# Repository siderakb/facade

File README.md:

# Facade60 Keyboard

- 60% mechanical keyboard kit, 2U LShift layout
- 65 keys, Cherry MX style hot-swappable
- Gasket mount
- CNC Aluminum top case
- MJF Nylon bottom case
- USB & RP2040 MCU daughterboard
- [QMK](https://qmk.fm/) and [Vial](https://get.vial.today/) support

[Demo video](https://youtu.be/Ful9dqWGcHk)

## Structure

- Top case
- Gaskets
- Plate
- Gaskets
- Optional sound absorbing foam
- PCB
- Optional case foam
- Bottom case
- Weight

## PCB

Daughterboard PCBA available.

### Board Characteristics

- Copper layer count: 2
- Board thickness: 1.6 mm
- Board overall dimensions
    - Main board: 285 mm x 99.1 mm
    - Daughterboard: 29.25 mm x 43.75 mm
- Min track/spacing: 0.15 mm / 0.15 mm
- Min hole diameter: 0.3 mm
- Castellated pads: No
- Edge card connectors: No
- Plated board edge: No

## Case

CAD files: [onshape](https://cad.onshape.com/documents/bbbe7399d3367f05c1e650e9/w/14fd774c6821c6187949e29b/e/877617ade201dbca93eed7b8)

### Screw

- 6* M2.5x10~12, OD < 5mm, for case
- 4* M2x2, 90° flat head, for weight
- 4* M2.5x3~5, OD <3.5mm, for PCB

## Firmware

[Vial-QMK](https://github.com/siderakb/vial-qmk/tree/siderakb/main/keyboards/siderakb/facade) (*siderakb/main* branch)

## License

Hardware available under the [CERN-OHL-P v2](/LICENSE) permissive license.

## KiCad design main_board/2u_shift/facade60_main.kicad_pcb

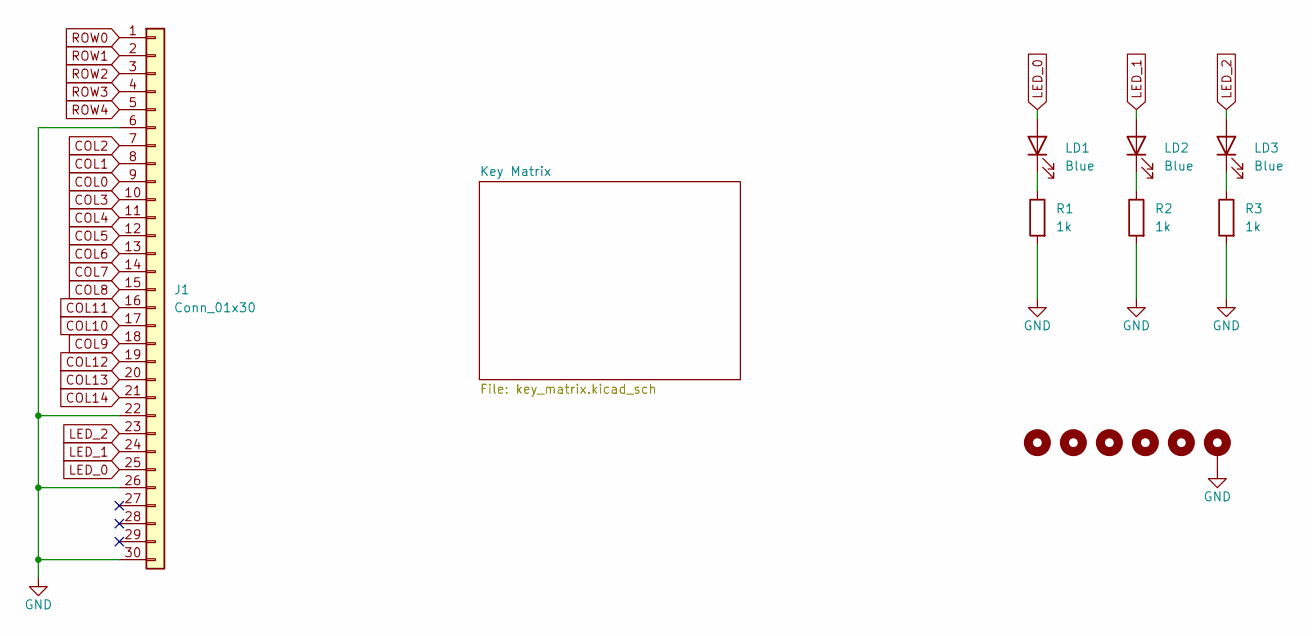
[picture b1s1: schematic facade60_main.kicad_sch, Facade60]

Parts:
H5, H6: MountingHole; MountingHole-C
H8, H9, H10: MountingHole_Pad; MountingHole-D
H11: MountingHole_Pad; MountingHole-B
J1: Conn_01x30; TE_3-1734839-0_1x30-1MP_P0.5mm_Horizontal
LD1, LD2, LD3: Blue; LED_0603_1608Metric; MFR. Part # 19-217/GHC-YR1S2/3T; LCSC C72043
R1, R2, R3: 1k; R_0603_1608Metric; MFR. Part # 0402WGF1001TCE; LCSC C11702

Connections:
COL0: J1.9; also elsewhere on the board
COL1: J1.8; also elsewhere on the board
COL2: J1.7; also elsewhere on the board
COL3: J1.10; also elsewhere on the board
COL4: J1.11; also elsewhere on the board
COL5: J1.12; also elsewhere on the board
COL6: J1.13; also elsewhere on the board
COL7: J1.14; also elsewhere on the board
COL8: J1.15; also elsewhere on the board
COL9: J1.18; also elsewhere on the board
COL10: J1.17; also elsewhere on the board
COL11: J1.16; also elsewhere on the board
COL12: J1.19; also elsewhere on the board
COL13: J1.20; also elsewhere on the board
COL14: J1.21; also elsewhere on the board
GND: H11.1, J1.6, J1.22, J1.26, J1.30, R1.2, R2.2, R3.2
LED_0: J1.25, LD1.2 (A)
LED_1: J1.24, LD2.2 (A)
LED_2: J1.23, LD3.2 (A)
unnamed: LD1.1 (K), R1.1
unnamed: LD2.1 (K), R2.1
unnamed: LD3.1 (K), R3.1
ROW0: J1.1; also elsewhere on the board
ROW1: J1.2; also elsewhere on the board
ROW2: J1.3; also elsewhere on the board
ROW3: J1.4; also elsewhere on the board
ROW4: J1.5; also elsewhere on the board

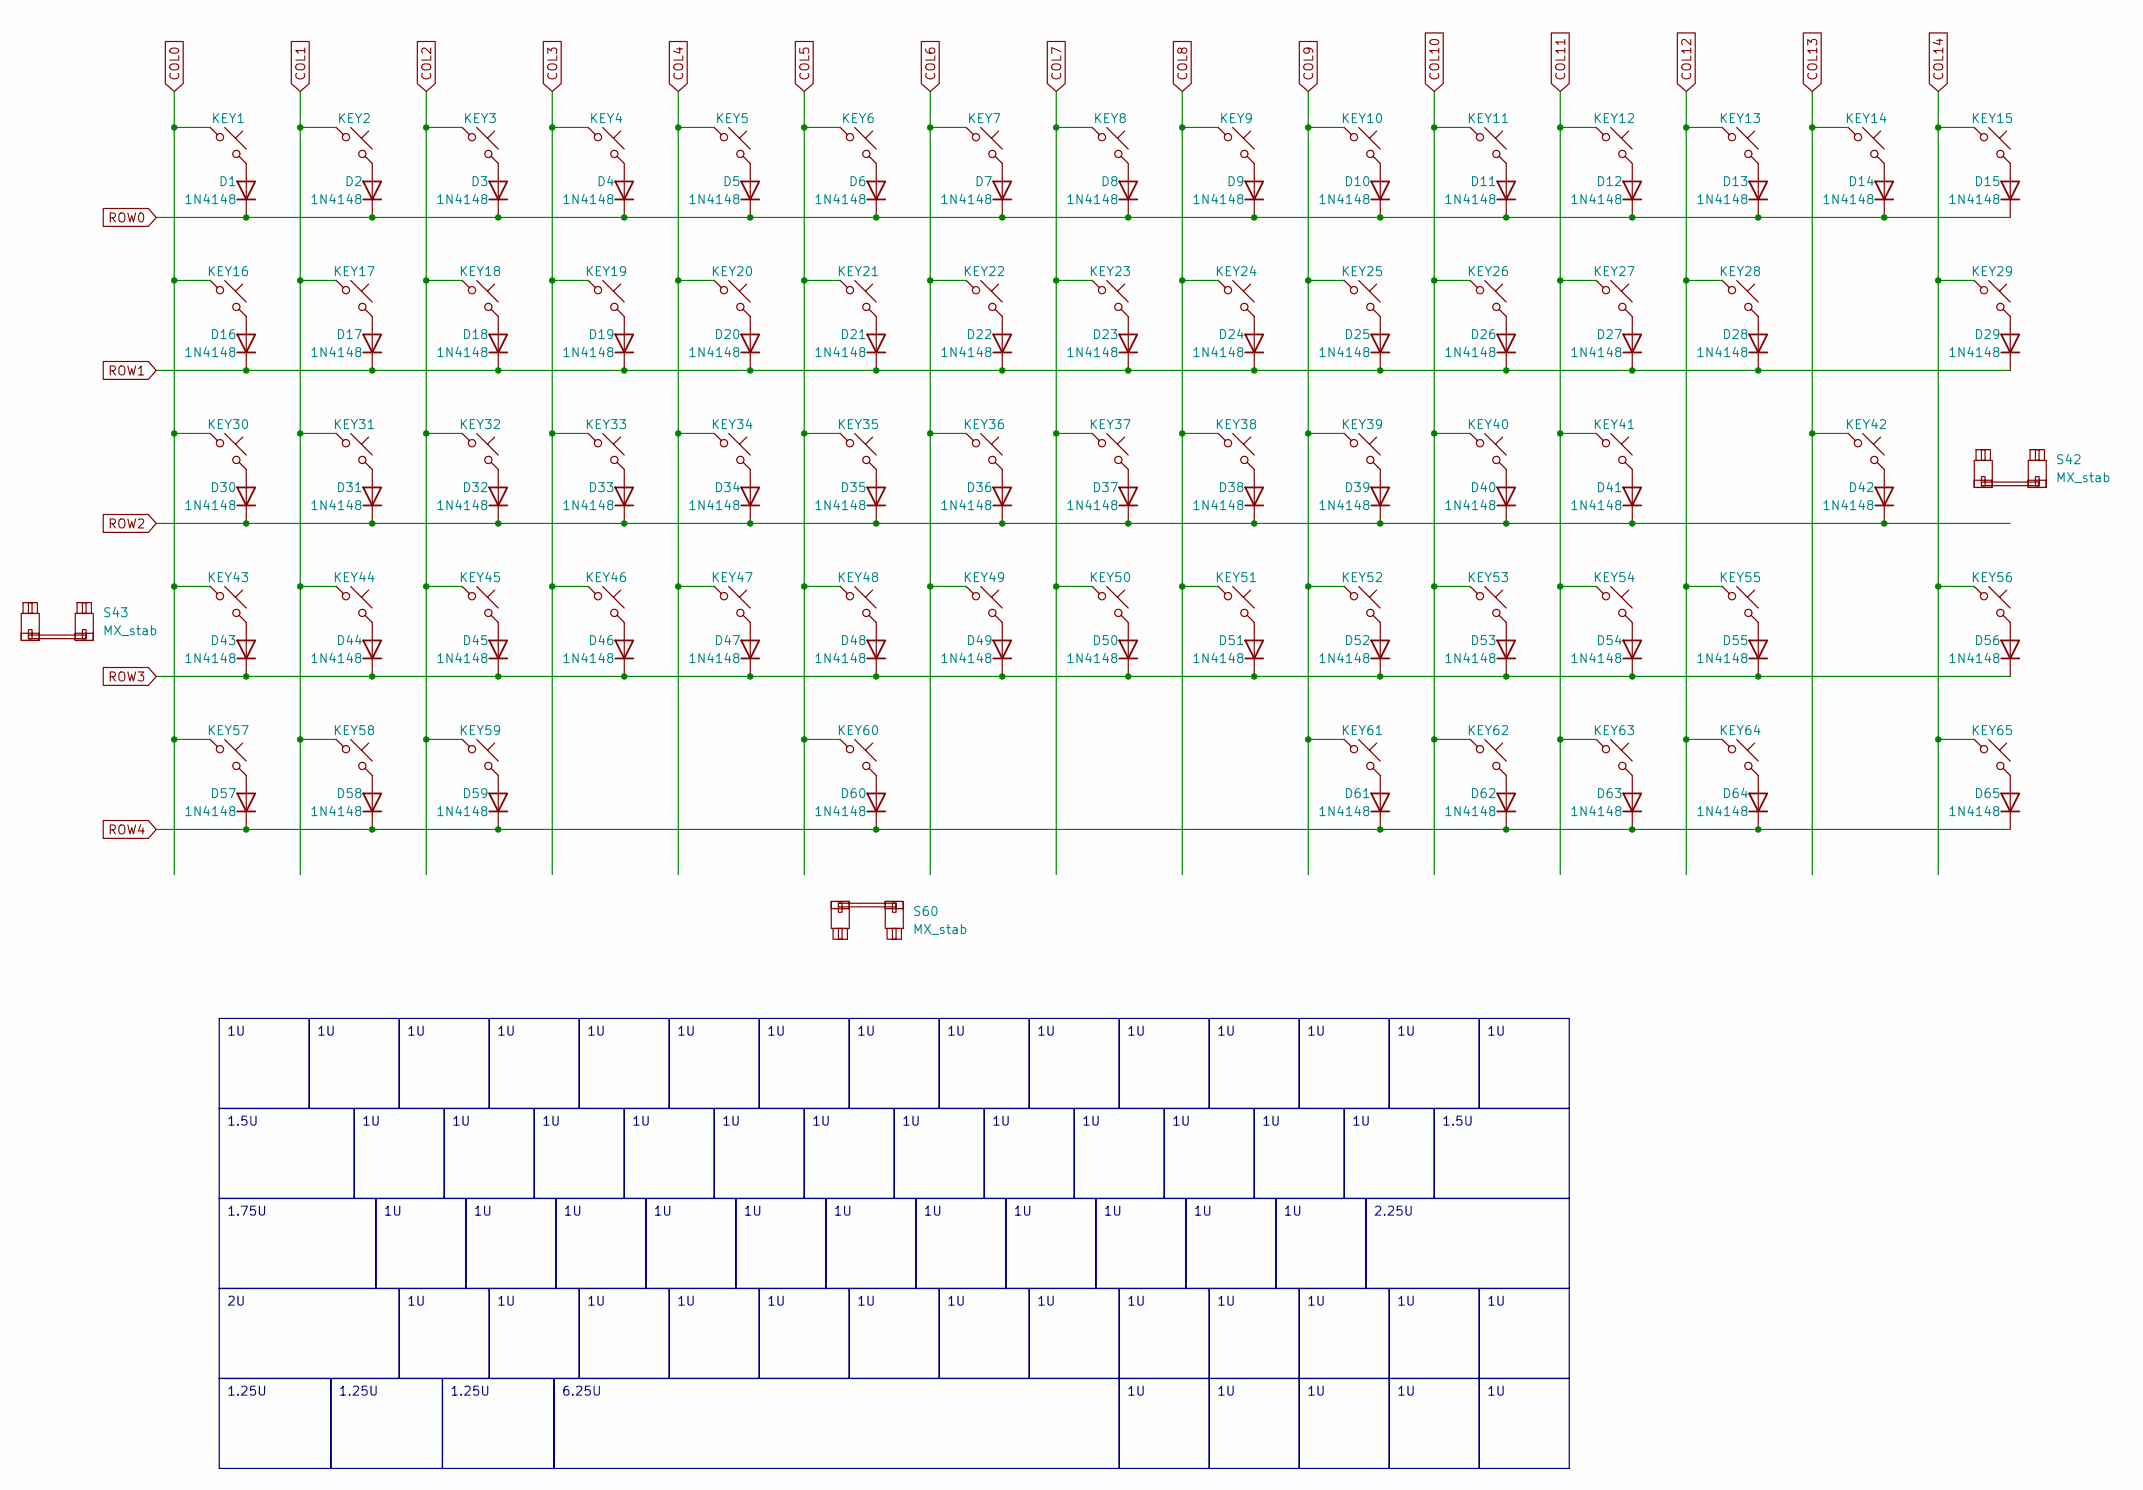
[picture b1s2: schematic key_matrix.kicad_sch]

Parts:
D1, D2, D3, D4, D5, D6, D7, D8, D9, D10, D11, D12, D13, D14, D15, D16, D17, D18, D19, D20, D21, D22, D23, D24, D25, D26, D27, D28, D29, D30, D31, D32, D33, D34, D35, D36, D37, D38, D39, D40, D41, D42, D43, D44, D45, D46, D47, D48, D49, D50, D51, D52, D53, D54, D55, D56, D57, D58, D59, D60, D61, D62, D63, D64, D65: 1N4148; D_SOD-323_HandSoldering; MFR. Part # 1N4148W; LCSC C81598
KEY1, KEY2, KEY3, KEY4, KEY5, KEY6, KEY7, KEY8, KEY9, KEY10, KEY11, KEY12, KEY13, KEY14, KEY15, KEY16, KEY17, KEY18, KEY19, KEY20, KEY21, KEY22, KEY23, KEY24, KEY25, KEY26, KEY27, KEY28, KEY29, KEY30, KEY31, KEY32, KEY33, KEY34, KEY35, KEY36, KEY37, KEY38, KEY39, KEY40, KEY41, KEY42, KEY43, KEY44, KEY45, KEY46, KEY47, KEY48, KEY49, KEY50, KEY51, KEY52, KEY53, KEY54, KEY55, KEY56, KEY57, KEY58, KEY59, KEY60, KEY61, KEY62, KEY63, KEY64, KEY65: SW_Push_45deg; SW_MX_HotSwap_PTH_nSilk
S42: MX_stab; STAB_MX_2.25u
S43: MX_stab; STAB_MX_2u
S60: MX_stab; STAB_MX_6.25u

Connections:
COL0: KEY1.1, KEY16.1, KEY30.1, KEY43.1, KEY57.1; also elsewhere on the board
COL1: KEY2.1, KEY17.1, KEY31.1, KEY44.1, KEY58.1; also elsewhere on the board
COL2: KEY3.1, KEY18.1, KEY32.1, KEY45.1, KEY59.1; also elsewhere on the board
COL3: KEY4.1, KEY19.1, KEY33.1, KEY46.1; also elsewhere on the board
COL4: KEY5.1, KEY20.1, KEY34.1, KEY47.1; also elsewhere on the board
COL5: KEY6.1, KEY21.1, KEY35.1, KEY48.1, KEY60.1; also elsewhere on the board
COL6: KEY7.1, KEY22.1, KEY36.1, KEY49.1; also elsewhere on the board
COL7: KEY8.1, KEY23.1, KEY37.1, KEY50.1; also elsewhere on the board
COL8: KEY9.1, KEY24.1, KEY38.1, KEY51.1; also elsewhere on the board
COL9: KEY10.1, KEY25.1, KEY39.1, KEY52.1, KEY61.1; also elsewhere on the board
COL10: KEY11.1, KEY26.1, KEY40.1, KEY53.1, KEY62.1; also elsewhere on the board
COL11: KEY12.1, KEY27.1, KEY41.1, KEY54.1, KEY63.1; also elsewhere on the board
COL12: KEY13.1, KEY28.1, KEY55.1, KEY64.1; also elsewhere on the board
COL13: KEY14.1, KEY42.1; also elsewhere on the board
COL14: KEY15.1, KEY29.1, KEY56.1, KEY65.1; also elsewhere on the board
unnamed: D1.2 (A), KEY1.2
unnamed: D2.2 (A), KEY2.2
unnamed: D3.2 (A), KEY3.2
unnamed: D4.2 (A), KEY4.2
unnamed: D5.2 (A), KEY5.2
unnamed: D6.2 (A), KEY6.2
unnamed: D7.2 (A), KEY7.2
unnamed: D8.2 (A), KEY8.2
unnamed: D9.2 (A), KEY9.2
unnamed: D10.2 (A), KEY10.2
unnamed: D11.2 (A), KEY11.2
unnamed: D12.2 (A), KEY12.2
unnamed: D13.2 (A), KEY13.2
unnamed: D14.2 (A), KEY14.2
unnamed: D15.2 (A), KEY15.2
unnamed: D16.2 (A), KEY16.2
unnamed: D17.2 (A), KEY17.2
unnamed: D18.2 (A), KEY18.2
unnamed: D19.2 (A), KEY19.2
unnamed: D20.2 (A), KEY20.2
unnamed: D21.2 (A), KEY21.2
unnamed: D22.2 (A), KEY22.2
unnamed: D23.2 (A), KEY23.2
unnamed: D24.2 (A), KEY24.2
unnamed: D25.2 (A), KEY25.2
unnamed: D26.2 (A), KEY26.2
unnamed: D27.2 (A), KEY27.2
unnamed: D28.2 (A), KEY28.2
unnamed: D29.2 (A), KEY29.2
unnamed: D30.2 (A), KEY30.2
unnamed: D31.2 (A), KEY31.2
unnamed: D32.2 (A), KEY32.2
unnamed: D33.2 (A), KEY33.2
unnamed: D34.2 (A), KEY34.2
unnamed: D35.2 (A), KEY35.2
unnamed: D36.2 (A), KEY36.2
unnamed: D37.2 (A), KEY37.2
unnamed: D38.2 (A), KEY38.2
unnamed: D39.2 (A), KEY39.2
unnamed: D40.2 (A), KEY40.2
unnamed: D41.2 (A), KEY41.2
unnamed: D42.2 (A), KEY42.2
unnamed: D43.2 (A), KEY43.2
unnamed: D44.2 (A), KEY44.2
unnamed: D45.2 (A), KEY45.2
unnamed: D46.2 (A), KEY46.2
unnamed: D47.2 (A), KEY47.2
unnamed: D48.2 (A), KEY48.2
unnamed: D49.2 (A), KEY49.2
unnamed: D50.2 (A), KEY50.2
unnamed: D51.2 (A), KEY51.2
unnamed: D52.2 (A), KEY52.2
unnamed: D53.2 (A), KEY53.2
unnamed: D54.2 (A), KEY54.2
unnamed: D55.2 (A), KEY55.2
unnamed: D56.2 (A), KEY56.2
unnamed: D57.2 (A), KEY57.2
unnamed: D58.2 (A), KEY58.2
unnamed: D59.2 (A), KEY59.2
unnamed: D60.2 (A), KEY60.2
unnamed: D61.2 (A), KEY61.2
unnamed: D62.2 (A), KEY62.2
unnamed: D63.2 (A), KEY63.2
unnamed: D64.2 (A), KEY64.2
unnamed: D65.2 (A), KEY65.2
ROW0: D1.1 (K), D2.1 (K), D3.1 (K), D4.1 (K), D5.1 (K), D6.1 (K), D7.1 (K), D8.1 (K), D9.1 (K), D10.1 (K), D11.1 (K), D12.1 (K), D13.1 (K), D14.1 (K), D15.1 (K); also elsewhere on the board
ROW1: D16.1 (K), D17.1 (K), D18.1 (K), D19.1 (K), D20.1 (K), D21.1 (K), D22.1 (K), D23.1 (K), D24.1 (K), D25.1 (K), D26.1 (K), D27.1 (K), D28.1 (K), D29.1 (K); also elsewhere on the board
ROW2: D30.1 (K), D31.1 (K), D32.1 (K), D33.1 (K), D34.1 (K), D35.1 (K), D36.1 (K), D37.1 (K), D38.1 (K), D39.1 (K), D40.1 (K), D41.1 (K), D42.1 (K); also elsewhere on the board
ROW3: D43.1 (K), D44.1 (K), D45.1 (K), D46.1 (K), D47.1 (K), D48.1 (K), D49.1 (K), D50.1 (K), D51.1 (K), D52.1 (K), D53.1 (K), D54.1 (K), D55.1 (K), D56.1 (K); also elsewhere on the board
ROW4: D57.1 (K), D58.1 (K), D59.1 (K), D60.1 (K), D61.1 (K), D62.1 (K), D63.1 (K), D64.1 (K), D65.1 (K); also elsewhere on the board

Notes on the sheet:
1.5U
2.25U
1.25U
6.25U
1.75U

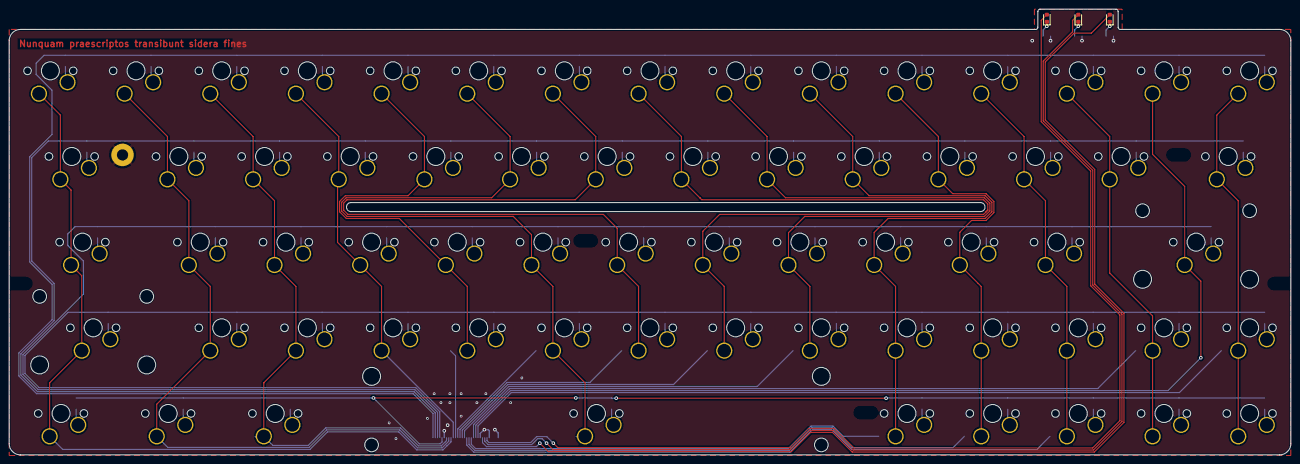
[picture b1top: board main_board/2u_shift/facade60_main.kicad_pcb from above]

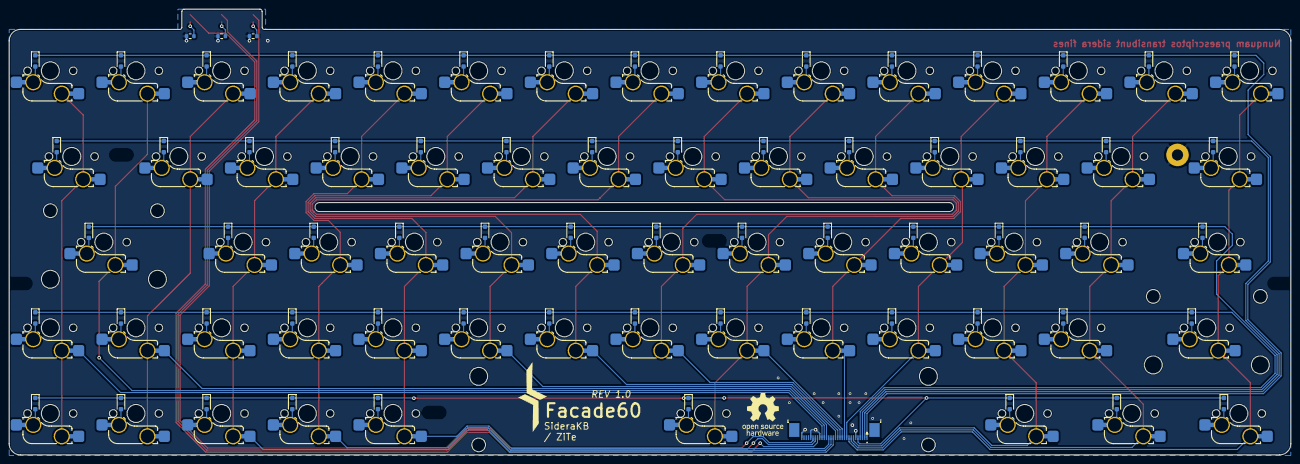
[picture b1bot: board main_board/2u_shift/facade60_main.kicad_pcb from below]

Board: 2 copper layers, 285.0 x 99.1 mm, 146 parts (69 on the bottom side), 92 nets.

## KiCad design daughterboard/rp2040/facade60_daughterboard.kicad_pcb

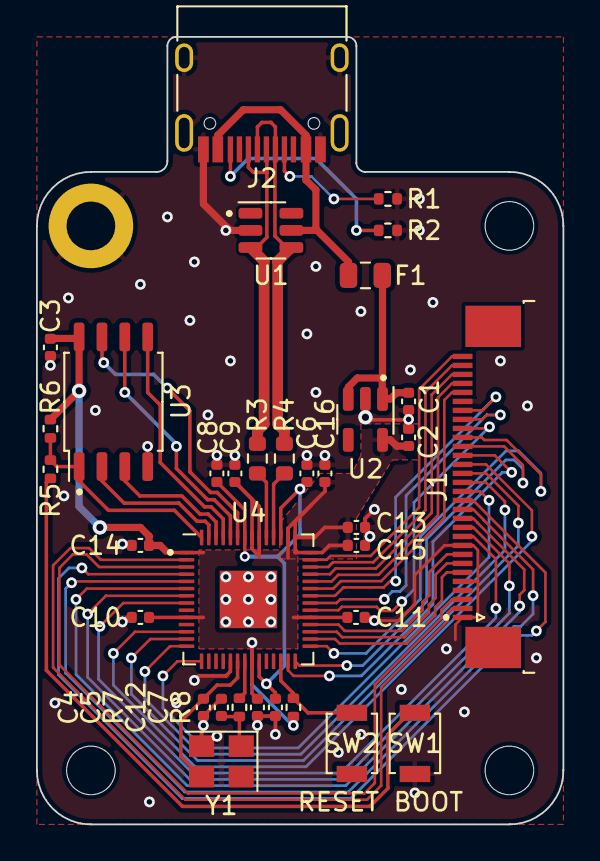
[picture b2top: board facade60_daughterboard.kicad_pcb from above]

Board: 2 copper layers, 29.2 x 43.8 mm, 38 parts (0 on the bottom side), 47 nets.

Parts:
C1, C2, C8, C16: 1uF; C_0402_1005Metric
C3, C6, C7, C9, C10, C11, C12, C13, C14, C15: 100nF; C_0402_1005Metric
C4, C5: 20pF; C_0402_1005Metric
F1: 500mA, 6V; Fuse_0805_2012Metric
H1: MountingHole; MountingHole_2.7mm_M2.5_DIN965_Pad
H2, H3, H4: MountingHole; MountingHole_2.7mm_M2.5
J1: Conn_01x30; TE_3-1734839-0_1x30-1MP_P0.5mm_Horizontal
J2: USB_C_Receptacle_USB2.0; USB_C_Receptacle_HRO_TYPE-C-31-M-12
R1, R2: 5.1k; R_0402_1005Metric
R3, R4: 27; R_0603_1608Metric
R5, R7: 1k; R_0402_1005Metric
R6, R8: 10k; R_0402_1005Metric
SW1: BOOT; SW_SPST_B3U-1000P
SW2: RESET; SW_SPST_B3U-1000P
U1: SRV05-4; SOT-23-6
U2: RT9013-33GB; SOT-23-5
U3: W25Q128JVS; SOIC-8_5.23x5.23mm_P1.27mm
U4: RP2040; QFN-56-1EP_7x7mm_P0.4mm_EP3.2x3.2mm
Y1: 12MHz; Crystal_SMD_3225-4Pin_3.2x2.5mm

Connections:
+1V1: C6.1, C7.1, C8.1, U4.23 (DVDD), U4.45 (VREG_VOUT), U4.50 (DVDD)
+3V3: C2.1, C3.1, C9.1, C10.1, C11.1, C12.1, C13.1, C14.1, C15.1, C16.1, R6.1, R8.1, U2.5 (VOUT), U3.8 (VCC), U4.1 (IOVDD), U4.10 (IOVDD), U4.22 (IOVDD), U4.33 (IOVDD), U4.42 (IOVDD), U4.43 (ADC_AVDD), U4.44 (VREG_IN), U4.48 (USB_VDD), U4.49 (IOVDD)
+5V: C1.1, F1.2, U2.1 (VIN), U2.3 (EN)
/MCU/BOOT: R5.1, SW1.2
/MCU/QSPI_D0: U3.5 (DI(IO0)), U4.53 (QSPI_SD0)
/MCU/QSPI_D1: U3.2 (DO(IO1)), U4.55 (QSPI_SD1)
/MCU/QSPI_D2: U3.3 (IO2), U4.54 (QSPI_SD2)
/MCU/QSPI_D3: U3.7 (IO3), U4.51 (QSPI_SD3)
/MCU/QSPI_SCLK: U3.6 (CLK), U4.52 (QSPI_SCLK)
/MCU/QSPI_SS: R5.2, R6.2, U3.1 (~CS), U4.56 (QSPI_SS)
/MCU/~RESET: R8.2, SW2.2, U4.26 (RUN)
COL0: J1.22, U4.34 (GPIO22)
COL1: J1.23, U4.35 (GPIO23)
COL2: J1.24, U4.36 (GPIO24)
COL3: J1.21, U4.29 (GPIO18)
COL4: J1.20, U4.28 (GPIO17)
COL5: J1.19, U4.27 (GPIO16)
COL6: J1.18, U4.12 (GPIO9)
COL7: J1.17, U4.13 (GPIO10)
COL8: J1.16, U4.14 (GPIO11)
COL9: J1.13, U4.5 (GPIO3)
COL10: J1.14, U4.4 (GPIO2)
COL11: J1.15, U4.15 (GPIO12)
COL12: J1.12, U4.6 (GPIO4)
COL13: J1.11, U4.7 (GPIO5)
COL14: J1.10, U4.8 (GPIO6)
EC_A: J1.3, U4.3 (GPIO1)
EC_B: J1.2, U4.2 (GPIO0)
GND: C1.2, C2.2, C3.2, C4.1, C5.1, C6.2, C7.2, C8.2, C9.2, C10.2, C11.2, C12.2, C13.2, C14.2, C15.2, C16.2, H1.1, J1.1, J1.5, J1.9, J1.25, J2.A1 (GND), J2.A12 (GND), J2.B1 (GND), J2.B12 (GND), J2.S1 (SHIELD), R1.2, R2.2, SW1.1, SW2.1, U1.2 (VN), U2.2 (GND), U3.4 (GND), U4.19 (TESTEN), U4.57 (GND), Y1.2, Y1.4
LED_0: J1.6, U4.30 (GPIO19)
LED_1: J1.7, U4.31 (GPIO20)
LED_2: J1.8, U4.32 (GPIO21)
unnamed: C5.2, R7.1, Y1.1
unnamed: J2.A5 (CC1), R1.1
unnamed: J2.B5 (CC2), R2.1
unnamed: R4.2, U4.46 (USB_DM)
unnamed: R3.2, U4.47 (USB_DP)
unnamed: C4.2, U4.20 (XIN), Y1.3
unnamed: R7.2, U4.21 (XOUT)
ROW0: J1.30, U4.41 (GPIO29_ADC3)
ROW1: J1.29, U4.40 (GPIO28_ADC2)
ROW2: J1.28, U4.39 (GPIO27_ADC1)
ROW3: J1.27, U4.38 (GPIO26_ADC0)
ROW4: J1.26, U4.37 (GPIO25)
USB_D+: J2.A6 (D+), J2.B6 (D+), R3.1, U1.3 (IO2)
USB_D-: J2.A7 (D-), J2.B7 (D-), R4.1, U1.4 (IO3)
VBUS: F1.1, J2.A4 (VBUS), J2.A9 (VBUS), J2.B4 (VBUS), J2.B9 (VBUS), U1.5 (VP)

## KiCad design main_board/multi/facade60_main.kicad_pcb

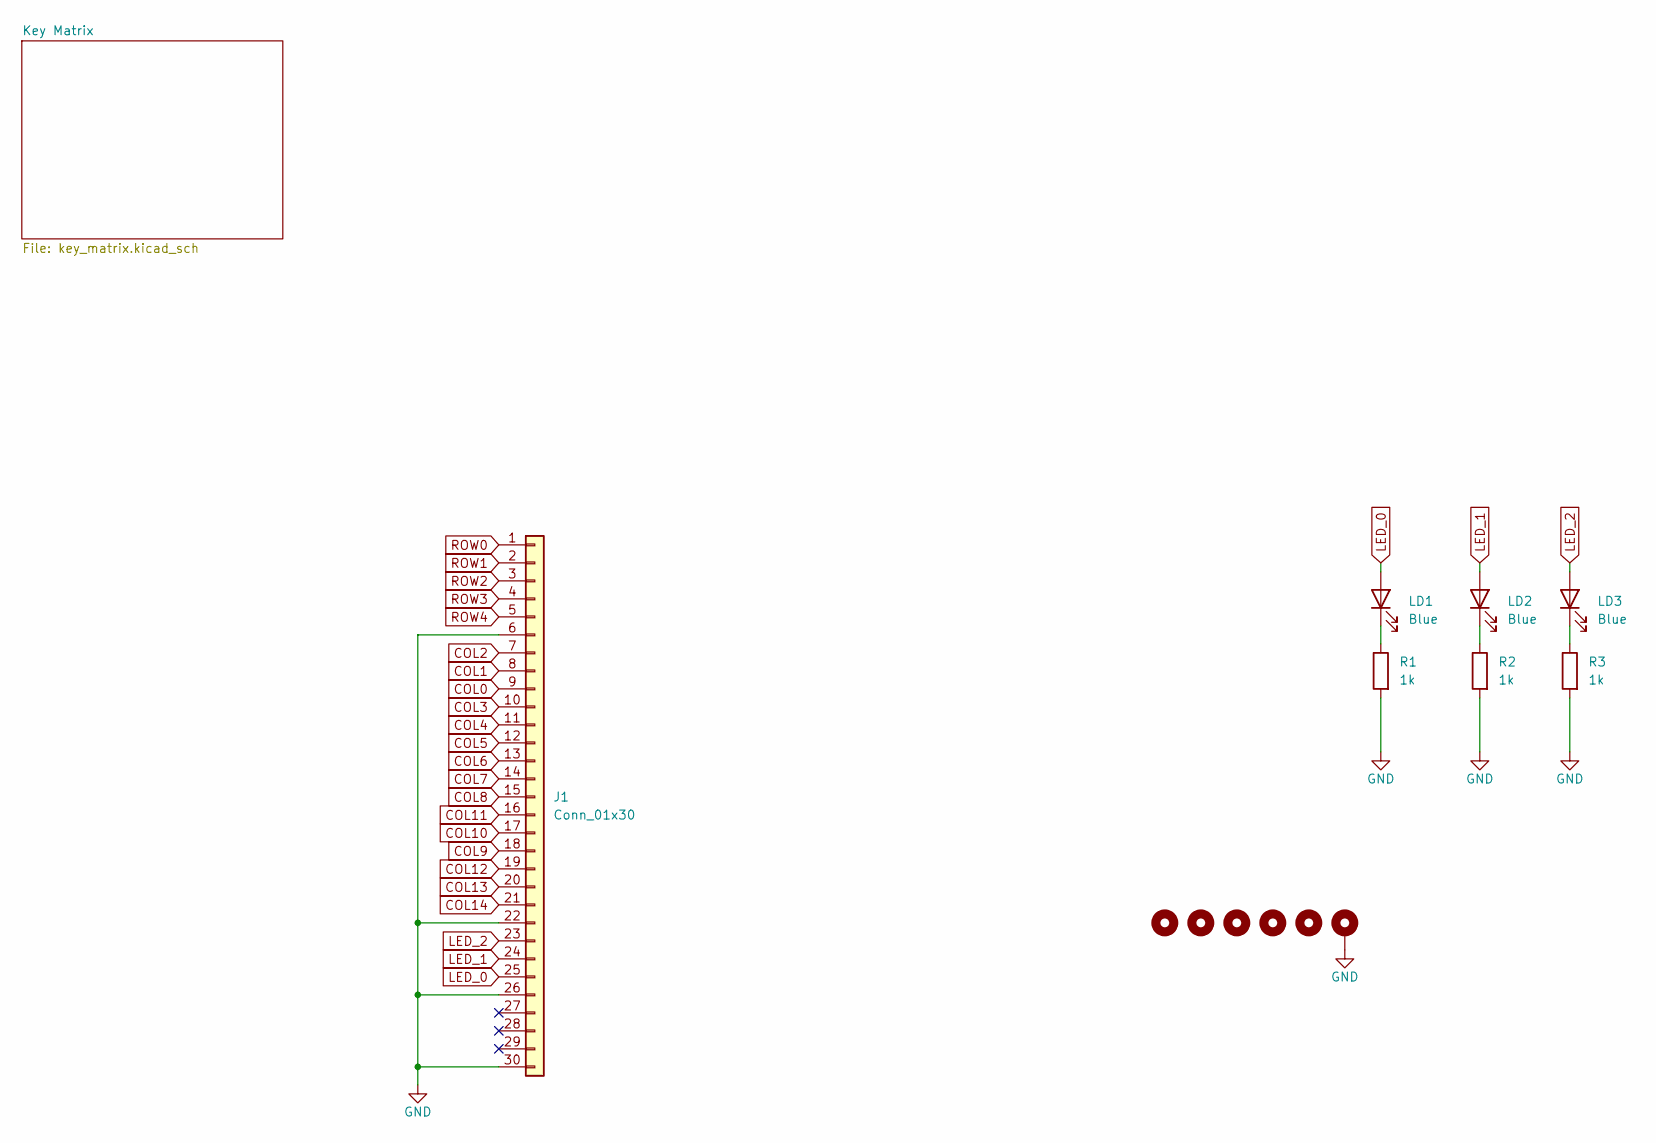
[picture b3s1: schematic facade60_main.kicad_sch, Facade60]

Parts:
H5, H6: MountingHole; MountingHole-C
H8, H9, H10: MountingHole_Pad; MountingHole-D
H11: MountingHole_Pad; MountingHole-B
J1: Conn_01x30; TE_3-1734839-0_1x30-1MP_P0.5mm_Horizontal
LD1, LD2, LD3: Blue; LED_0603_1608Metric; MFR. Part # 19-217/GHC-YR1S2/3T; LCSC C72043
R1, R2, R3: 1k; R_0603_1608Metric; MFR. Part # 0402WGF1001TCE; LCSC C11702

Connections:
COL0: J1.9; also elsewhere on the board
COL1: J1.8; also elsewhere on the board
COL2: J1.7; also elsewhere on the board
COL3: J1.10; also elsewhere on the board
COL4: J1.11; also elsewhere on the board
COL5: J1.12; also elsewhere on the board
COL6: J1.13; also elsewhere on the board
COL7: J1.14; also elsewhere on the board
COL8: J1.15; also elsewhere on the board
COL9: J1.18; also elsewhere on the board
COL10: J1.17; also elsewhere on the board
COL11: J1.16; also elsewhere on the board
COL12: J1.19; also elsewhere on the board
COL13: J1.20; also elsewhere on the board
COL14: J1.21; also elsewhere on the board
GND: H11.1, J1.6, J1.22, J1.26, J1.30, R1.2, R2.2, R3.2
LED_0: J1.25, LD1.2 (A)
LED_1: J1.24, LD2.2 (A)
LED_2: J1.23, LD3.2 (A)
unnamed: LD1.1 (K), R1.1
unnamed: LD2.1 (K), R2.1
unnamed: LD3.1 (K), R3.1
ROW0: J1.1; also elsewhere on the board
ROW1: J1.2; also elsewhere on the board
ROW2: J1.3; also elsewhere on the board
ROW3: J1.4; also elsewhere on the board
ROW4: J1.5; also elsewhere on the board

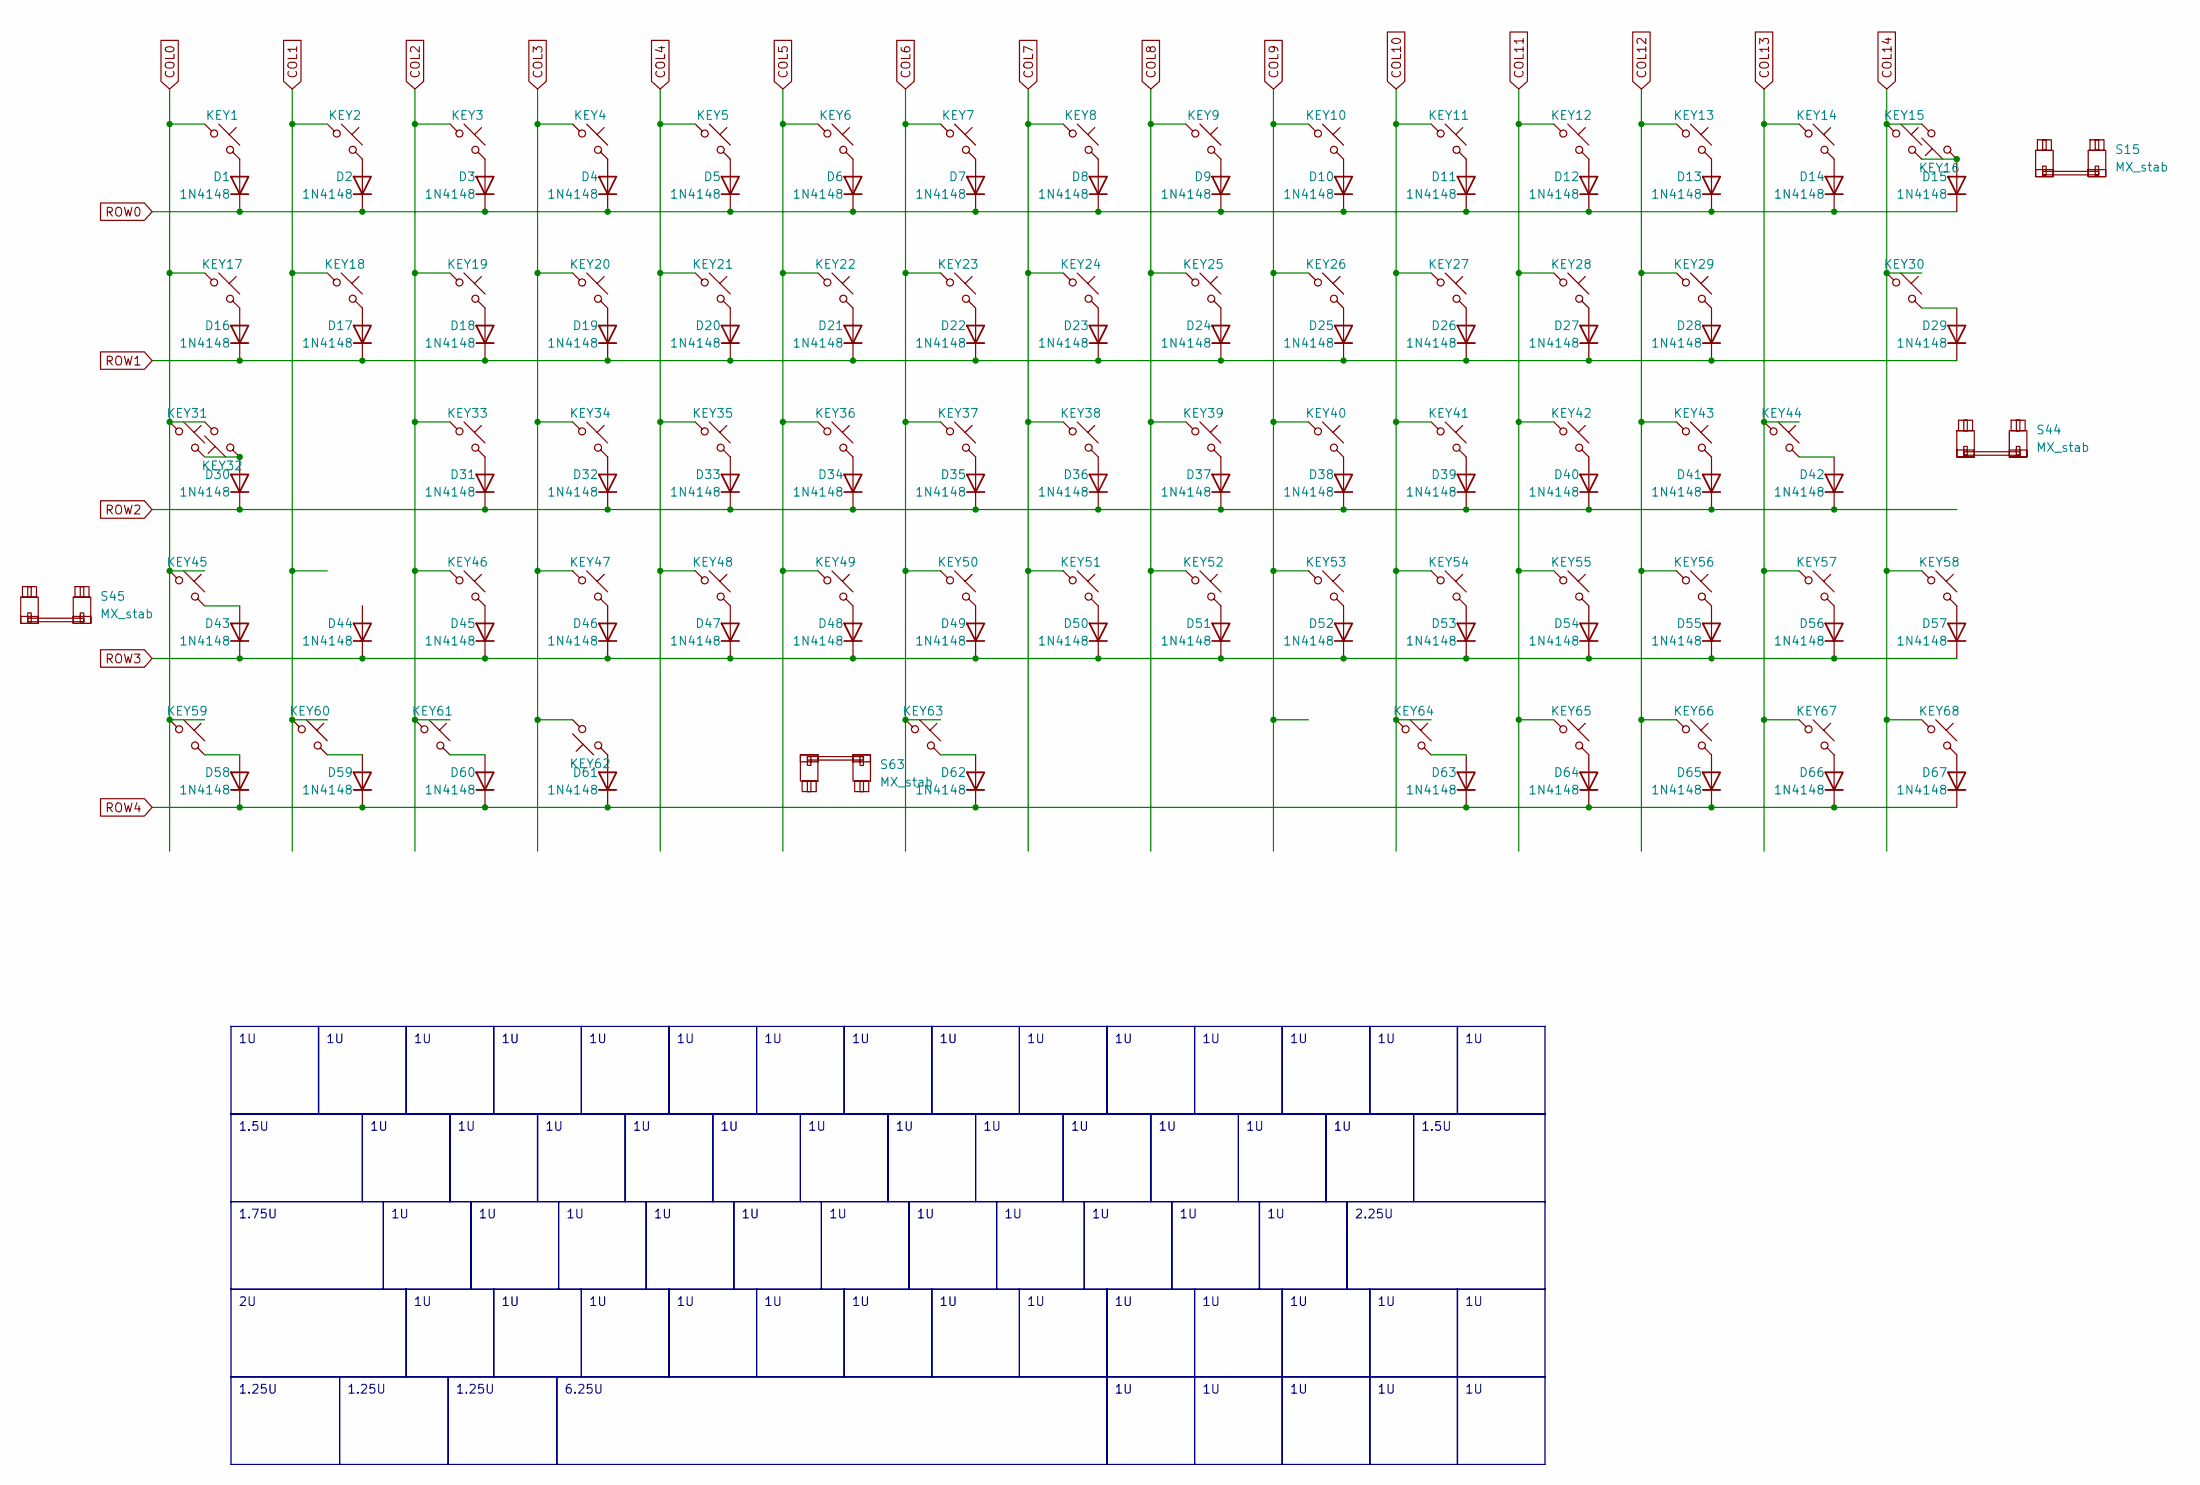
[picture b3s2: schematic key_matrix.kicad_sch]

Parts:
D1, D2, D3, D4, D5, D6, D7, D8, D9, D10, D11, D12, D13, D14, D15, D16, D17, D18, D19, D20, D21, D22, D23, D24, D25, D26, D27, D28, D29, D30, D31, D32, D33, D34, D35, D36, D37, D38, D39, D40, D41, D42, D43, D44, D45, D46, D47, D48, D49, D50, D51, D52, D53, D54, D55, D56, D57, D58, D59, D60, D61, D62, D63, D64, D65, D66, D67: 1N4148; D_SOD-323_HandSoldering; MFR. Part # 1N4148W; LCSC C81598
KEY1, KEY2, KEY3, KEY4, KEY5, KEY6, KEY7, KEY8, KEY9, KEY10, KEY11, KEY12, KEY13, KEY14, KEY15, KEY16, KEY17, KEY18, KEY19, KEY20, KEY21, KEY22, KEY23, KEY24, KEY25, KEY26, KEY27, KEY28, KEY29, KEY30, KEY31, KEY32, KEY33, KEY34, KEY35, KEY36, KEY37, KEY38, KEY39, KEY40, KEY41, KEY42, KEY43, KEY44, KEY45, KEY46, KEY47, KEY48, KEY49, KEY50, KEY51, KEY52, KEY53, KEY54, KEY55, KEY56, KEY57, KEY58, KEY59, KEY60, KEY61, KEY62, KEY63, KEY64, KEY65, KEY66, KEY67, KEY68: SW_Push_45deg; SW_MX_HotSwap_PTH
S15, S45: MX_stab; STAB_MX_2u
S44: MX_stab; STAB_MX_2.25u
S63: MX_stab; STAB_MX_6.25u

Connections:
COL0: KEY1.1, KEY17.1, KEY31.1, KEY32.2, KEY45.1, KEY59.1; also elsewhere on the board
COL1: KEY2.1, KEY18.1, KEY60.1; also elsewhere on the board
COL2: KEY3.1, KEY19.1, KEY33.1, KEY46.1, KEY61.1; also elsewhere on the board
COL3: KEY4.1, KEY20.1, KEY34.1, KEY47.1, KEY62.2; also elsewhere on the board
COL4: KEY5.1, KEY21.1, KEY35.1, KEY48.1; also elsewhere on the board
COL5: KEY6.1, KEY22.1, KEY36.1, KEY49.1; also elsewhere on the board
COL6: KEY7.1, KEY23.1, KEY37.1, KEY50.1, KEY63.1; also elsewhere on the board
COL7: KEY8.1, KEY24.1, KEY38.1, KEY51.1; also elsewhere on the board
COL8: KEY9.1, KEY25.1, KEY39.1, KEY52.1; also elsewhere on the board
COL9: KEY10.1, KEY26.1, KEY40.1, KEY53.1; also elsewhere on the board
COL10: KEY11.1, KEY27.1, KEY41.1, KEY54.1, KEY64.1; also elsewhere on the board
COL11: KEY12.1, KEY28.1, KEY42.1, KEY55.1, KEY65.1; also elsewhere on the board
COL12: KEY13.1, KEY29.1, KEY43.1, KEY56.1, KEY66.1; also elsewhere on the board
COL13: KEY14.1, KEY44.1, KEY57.1, KEY67.1; also elsewhere on the board
COL14: KEY15.1, KEY16.2, KEY30.1, KEY58.1, KEY68.1; also elsewhere on the board
unnamed: D1.2 (A), KEY1.2
unnamed: D2.2 (A), KEY2.2
unnamed: D3.2 (A), KEY3.2
unnamed: D4.2 (A), KEY4.2
unnamed: D5.2 (A), KEY5.2
unnamed: D6.2 (A), KEY6.2
unnamed: D7.2 (A), KEY7.2
unnamed: D8.2 (A), KEY8.2
unnamed: D9.2 (A), KEY9.2
unnamed: D10.2 (A), KEY10.2
unnamed: D11.2 (A), KEY11.2
unnamed: D12.2 (A), KEY12.2
unnamed: D13.2 (A), KEY13.2
unnamed: D14.2 (A), KEY14.2
unnamed: D15.2 (A), KEY15.2, KEY16.1
unnamed: D16.2 (A), KEY17.2
unnamed: D17.2 (A), KEY18.2
unnamed: D18.2 (A), KEY19.2
unnamed: D19.2 (A), KEY20.2
unnamed: D20.2 (A), KEY21.2
unnamed: D21.2 (A), KEY22.2
unnamed: D22.2 (A), KEY23.2
unnamed: D23.2 (A), KEY24.2
unnamed: D24.2 (A), KEY25.2
unnamed: D25.2 (A), KEY26.2
unnamed: D26.2 (A), KEY27.2
unnamed: D27.2 (A), KEY28.2
unnamed: D28.2 (A), KEY29.2
unnamed: D29.2 (A), KEY30.2
unnamed: D30.2 (A), KEY31.2, KEY32.1
unnamed: D31.2 (A), KEY33.2
unnamed: D32.2 (A), KEY34.2
unnamed: D33.2 (A), KEY35.2
unnamed: D34.2 (A), KEY36.2
unnamed: D35.2 (A), KEY37.2
unnamed: D36.2 (A), KEY38.2
unnamed: D37.2 (A), KEY39.2
unnamed: D38.2 (A), KEY40.2
unnamed: D39.2 (A), KEY41.2
unnamed: D40.2 (A), KEY42.2
unnamed: D41.2 (A), KEY43.2
unnamed: D42.2 (A), KEY44.2
unnamed: D43.2 (A), KEY45.2
unnamed: D45.2 (A), KEY46.2
unnamed: D46.2 (A), KEY47.2
unnamed: D47.2 (A), KEY48.2
unnamed: D48.2 (A), KEY49.2
unnamed: D49.2 (A), KEY50.2
unnamed: D50.2 (A), KEY51.2
unnamed: D51.2 (A), KEY52.2
unnamed: D52.2 (A), KEY53.2
unnamed: D53.2 (A), KEY54.2
unnamed: D54.2 (A), KEY55.2
unnamed: D55.2 (A), KEY56.2
unnamed: D56.2 (A), KEY57.2
unnamed: D57.2 (A), KEY58.2
unnamed: D58.2 (A), KEY59.2
unnamed: D59.2 (A), KEY60.2
unnamed: D60.2 (A), KEY61.2
unnamed: D61.2 (A), KEY62.1
unnamed: D62.2 (A), KEY63.2
unnamed: D63.2 (A), KEY64.2
unnamed: D64.2 (A), KEY65.2
unnamed: D65.2 (A), KEY66.2
unnamed: D66.2 (A), KEY67.2
unnamed: D67.2 (A), KEY68.2
ROW0: D1.1 (K), D2.1 (K), D3.1 (K), D4.1 (K), D5.1 (K), D6.1 (K), D7.1 (K), D8.1 (K), D9.1 (K), D10.1 (K), D11.1 (K), D12.1 (K), D13.1 (K), D14.1 (K), D15.1 (K); also elsewhere on the board
ROW1: D16.1 (K), D17.1 (K), D18.1 (K), D19.1 (K), D20.1 (K), D21.1 (K), D22.1 (K), D23.1 (K), D24.1 (K), D25.1 (K), D26.1 (K), D27.1 (K), D28.1 (K), D29.1 (K); also elsewhere on the board
ROW2: D30.1 (K), D31.1 (K), D32.1 (K), D33.1 (K), D34.1 (K), D35.1 (K), D36.1 (K), D37.1 (K), D38.1 (K), D39.1 (K), D40.1 (K), D41.1 (K), D42.1 (K); also elsewhere on the board
ROW3: D43.1 (K), D44.1 (K), D45.1 (K), D46.1 (K), D47.1 (K), D48.1 (K), D49.1 (K), D50.1 (K), D51.1 (K), D52.1 (K), D53.1 (K), D54.1 (K), D55.1 (K), D56.1 (K), D57.1 (K); also elsewhere on the board
ROW4: D58.1 (K), D59.1 (K), D60.1 (K), D61.1 (K), D62.1 (K), D63.1 (K), D64.1 (K), D65.1 (K), D66.1 (K), D67.1 (K); also elsewhere on the board

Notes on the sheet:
1.5U
2.25U
1.25U
6.25U
1.75U

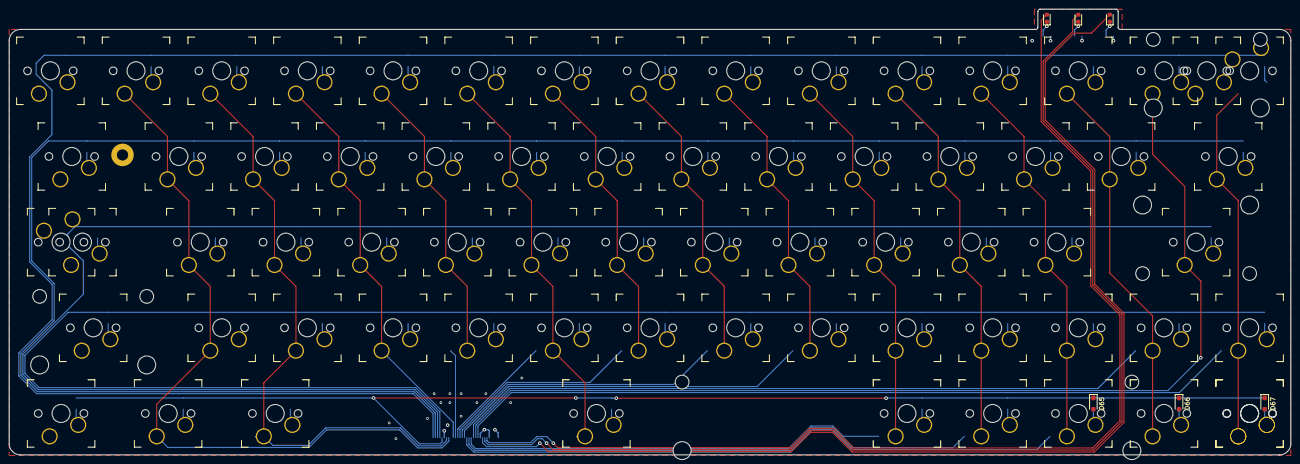
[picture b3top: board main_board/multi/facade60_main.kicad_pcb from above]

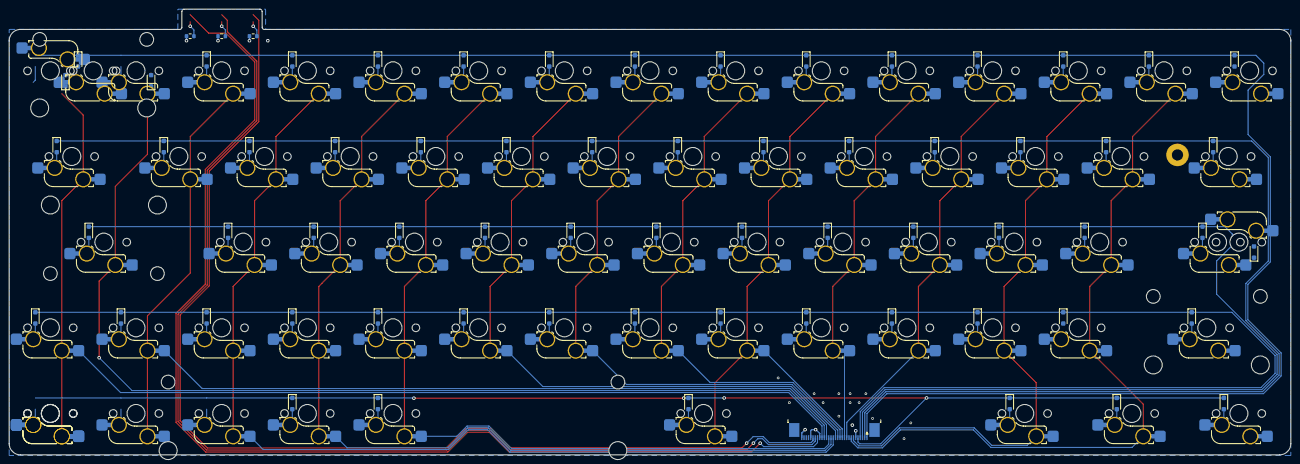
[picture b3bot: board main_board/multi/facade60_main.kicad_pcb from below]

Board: 2 copper layers, 285.0 x 99.1 mm, 152 parts (68 on the bottom side), 93 nets.

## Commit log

2024-01-03 Add KiCad project
2024-01-03 Add multi layout projcet
2024-01-03 Create LICENSE
2024-01-05 Replace R1 & R2 to 0402
2024-02-13 Update KLE files
2025-04-17 chore: add `.gitattributes`

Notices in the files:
daughterboard/rp2040/facade60_daughterboard.kicad_pcb:
Open source hardware, CERN-OHL-P v2
